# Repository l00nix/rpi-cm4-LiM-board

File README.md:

---
---

{% include readme_header.html %}
{% include README.html %}

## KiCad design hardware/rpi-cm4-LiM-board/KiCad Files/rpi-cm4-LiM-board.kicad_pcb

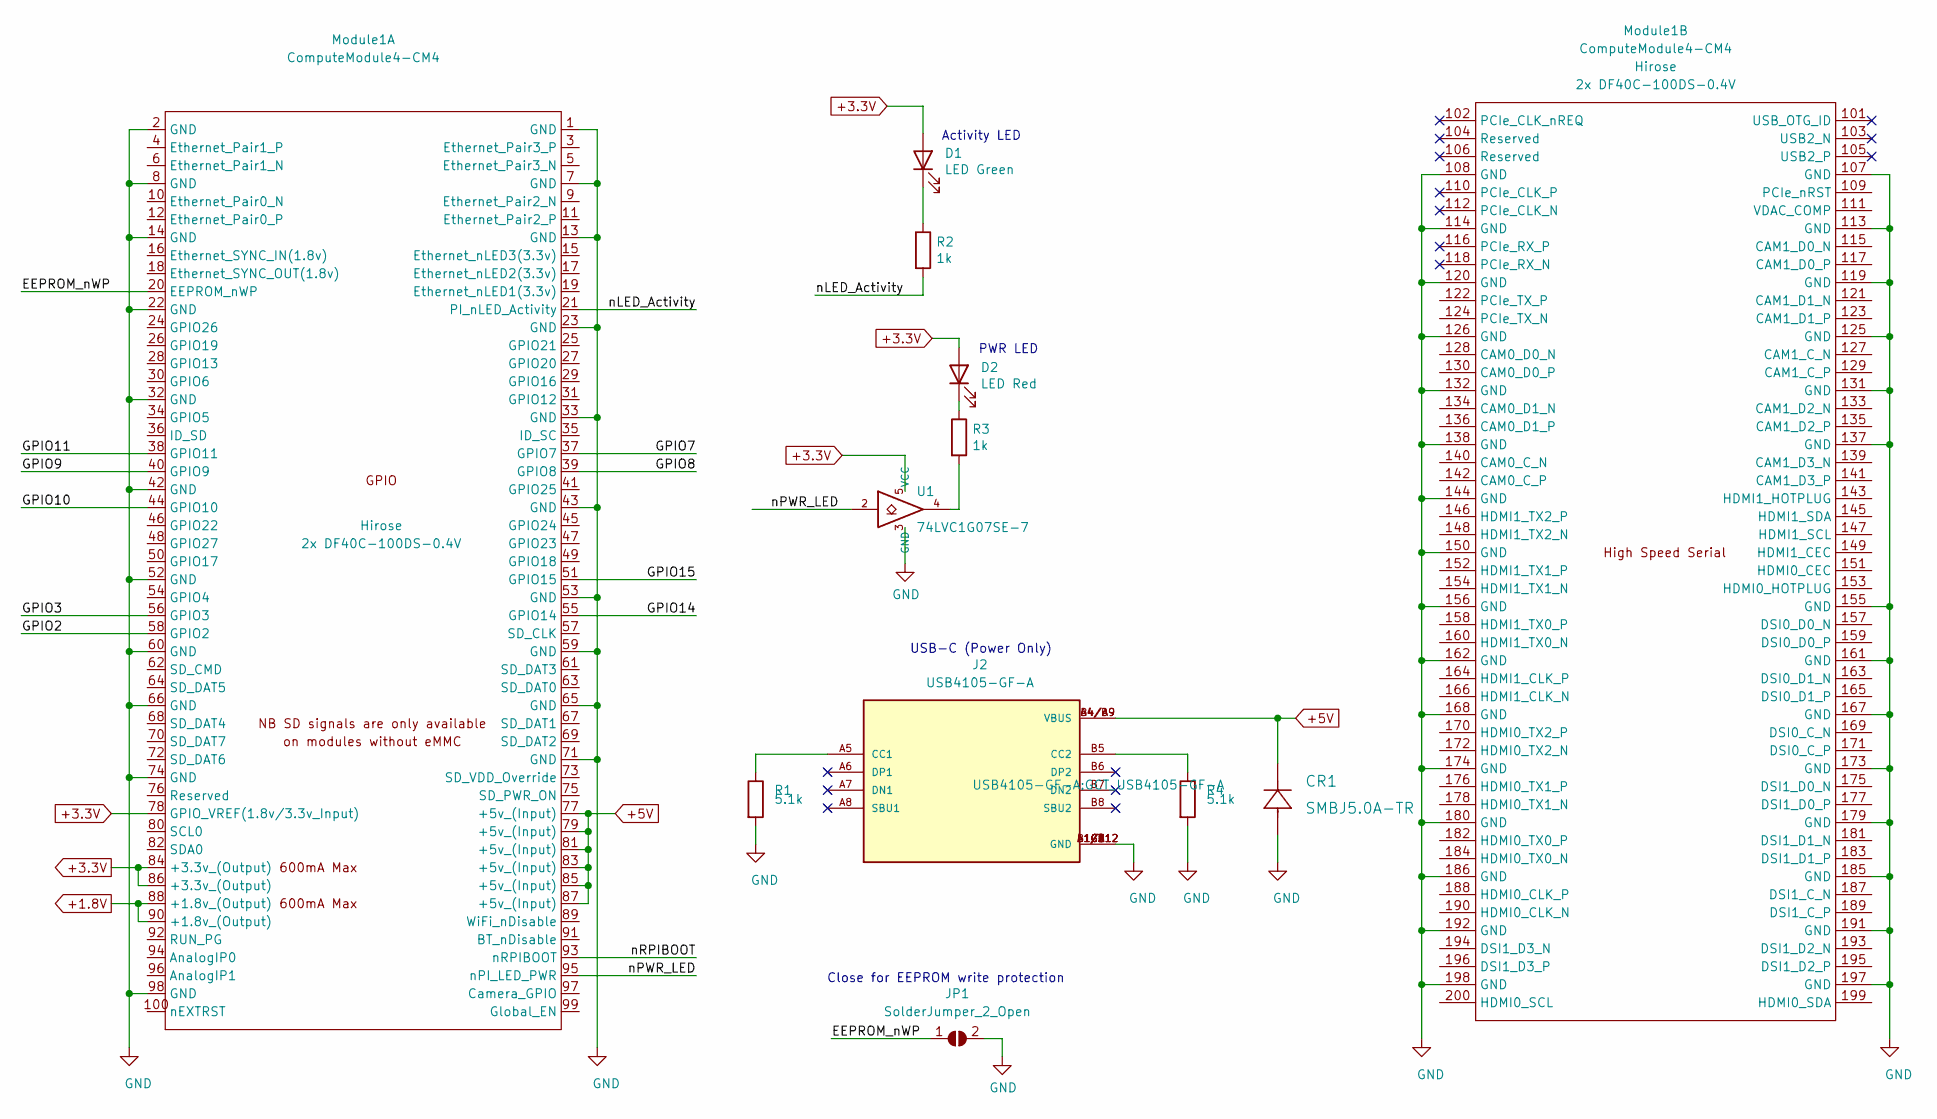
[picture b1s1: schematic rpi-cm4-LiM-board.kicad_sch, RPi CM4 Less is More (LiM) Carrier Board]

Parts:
CR1: SMBJ5.0A-TR; MPN SMBJ5.0A-TR; Digi-Key_PN 497-3144-1-ND
D1: LED Green; LED_0603_1608Metric; Part Description Green 572nm LED Indication - Discrete 2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; Digi-Key_PN 160-1478-1-ND
D2: LED Red; LED_0603_1608Metric; Part Description Red 620nm LED Indication - Discrete 2.2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; Digi-Key_PN 160-1479-1-ND
J2: USB4105-GF-A; GCT_USB4105-GF-A; MPN USB4105-GF-A; Digi-Key_PN 2073-USB4105-GF-ACT-ND
JP1: SolderJumper_2_Open; SolderJumper-2_P1.3mm_Open_RoundedPad1.0x1.5mm
Module1: ComputeModule4-CM4; Raspberry-Pi-4-Compute-Module; MPN 2x DF40C-100DS-0.4V; Digi-Key_PN 2x H11615CT-ND
R1, R4: 5.1k; R_0603_1608Metric_Pad0.98x0.95mm_HandSolder; MPN RC0603FR-075K1L; Digi-Key_PN 311-5.10KHRCT-ND
R2, R3: 1k; R_0603_1608Metric_Pad0.98x0.95mm_HandSolder; MPN RC0603FR-071KL; Digi-Key_PN 311-1.00KHRCT-ND
U1: 74LVC1G07SE-7; SOT-353_SC-70-5; Part Description Buffer, Non-Inverting 1 Element 1 Bit p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; Digi-Key_PN 74LVC1G07SE-7DICT-ND

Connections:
+1.8V: Module1.88 (+1.8v_(Output)), Module1.90 (+1.8v_(Output))
+3.3V: D1.2 (A), D2.2 (A), Module1.78 (GPIO_VREF(1.8v/3.3v_Input)), Module1.84 (+3.3v_(Output)), Module1.86 (+3.3v_(Output)), U1.5 (VCC)
+5V: CR1.1, J2.A4/B9 (VBUS), J2.B4/A9 (VBUS), Module1.77 (+5v_(Input)), Module1.79 (+5v_(Input)), Module1.81 (+5v_(Input)), Module1.83 (+5v_(Input)), Module1.85 (+5v_(Input)), Module1.87 (+5v_(Input))
/CM4 GPIO/EEPROM_nWP: JP1.1 (A), Module1.20 (EEPROM_nWP)
/CM4 GPIO/GPIO2: Module1.58 (GPIO2)
/CM4 GPIO/GPIO3: Module1.56 (GPIO3)
/CM4 GPIO/GPIO7: Module1.37 (GPIO7)
/CM4 GPIO/GPIO8: Module1.39 (GPIO8)
/CM4 GPIO/GPIO9: Module1.40 (GPIO9)
/CM4 GPIO/GPIO10: Module1.44 (GPIO10)
/CM4 GPIO/GPIO11: Module1.38 (GPIO11)
/CM4 GPIO/GPIO14: Module1.55 (GPIO14)
/CM4 GPIO/GPIO15: Module1.51 (GPIO15)
/CM4 GPIO/nLED_Activity: Module1.21 (PI_nLED_Activity), R2.2
/CM4 GPIO/nPWR_LED: Module1.95 (nPI_LED_PWR), U1.2
/CM4 GPIO/nRPIBOOT: Module1.93 (nRPIBOOT)
GND: CR1.2, J2.A1/B12 (GND), J2.B1/A12 (GND), J2.G1 (GND), J2.G2 (GND), J2.G3 (GND), J2.G4 (GND), JP1.2 (B), Module1.1 (GND), Module1.2 (GND), Module1.7 (GND), Module1.8 (GND), Module1.13 (GND), Module1.14 (GND), Module1.22 (GND), Module1.23 (GND), Module1.32 (GND), Module1.33 (GND), Module1.42 (GND), Module1.43 (GND), Module1.52 (GND), Module1.53 (GND), Module1.59 (GND), Module1.60 (GND), Module1.65 (GND), Module1.66 (GND), Module1.71 (GND), Module1.74 (GND), Module1.98 (GND), Module1.107 (GND), Module1.108 (GND), Module1.113 (GND), Module1.114 (GND), Module1.119 (GND), Module1.120 (GND), Module1.125 (GND), Module1.126 (GND), Module1.131 (GND), Module1.132 (GND), Module1.137 (GND), Module1.138 (GND), Module1.144 (GND), Module1.150 (GND), Module1.155 (GND), Module1.156 (GND), Module1.161 (GND), Module1.162 (GND), Module1.167 (GND), Module1.168 (GND), Module1.173 (GND), Module1.174 (GND), Module1.179 (GND), Module1.180 (GND), Module1.185 (GND), Module1.186 (GND), Module1.191 (GND), Module1.192 (GND), Module1.197 (GND), Module1.198 (GND), R1.2, R4.2, U1.3 (GND)
unnamed: D1.1 (K), R2.1
unnamed 18: D2.1 (K), R3.1; also elsewhere on the board
unnamed: J2.A5 (CC1), R1.1
unnamed: J2.B5 (CC2), R4.1
unnamed 21: R3.2, U1.4; also elsewhere on the board

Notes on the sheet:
Activity LED
PWR LED
USB-C (Power Only)
Close for EEPROM write protection

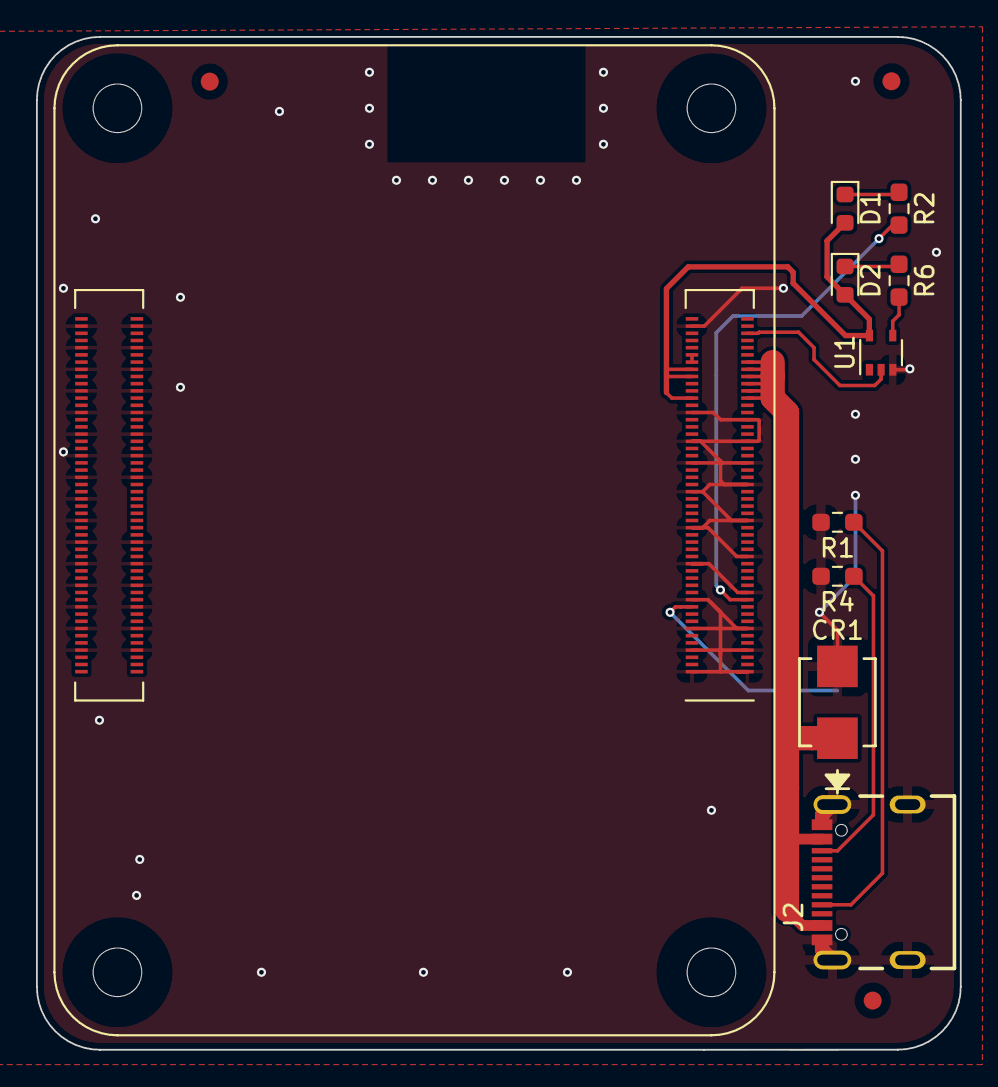
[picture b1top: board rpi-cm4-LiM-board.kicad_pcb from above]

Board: 2 copper layers, 51.3 x 56.3 mm, 11 parts (1 on the bottom side), 12 nets.

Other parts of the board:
R6: 1k; R_0603_1608Metric_Pad0.98x0.95mm_HandSolder

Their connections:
unnamed 18: R6.1; also elsewhere on the board
unnamed 21: R6.2; also elsewhere on the board

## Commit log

2021-07-24 added LiM+ board pages and other updates to KiCad files and renderings
2021-07-24 fix spelling mistakes, updated pictures sizes and fixed links
2021-07-24 minor edits and resized pictures
2021-07-24 minor edits
2021-07-26 LiM Carrier Board series website - second release
2021-07-26 fixed link in cookie_consent
2021-07-27 updated google analytics
2021-08-02 updated LiM board with heatsink screws and added pictures
2021-08-05 KiCad updates 3D iamges
2022-05-28 added back to top button and prepped cluster board page
2022-05-28 rejigged index and readme
2022-05-28 rejigged index and readme v2
2022-05-28 fixed README
2023-01-02 Updates for LiM CM4 Cluster Board

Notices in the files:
hardware/rpi-cm4-LiM-board/KiCad Files/rpi-cm4-LiM-board.kicad_pcb:
creativecommons.org/licenses/by/4.0
License: CC BY-SA 4.0
parts and their libraries:
Copyright 2016 Accelerated Designs. All rights reserved.
